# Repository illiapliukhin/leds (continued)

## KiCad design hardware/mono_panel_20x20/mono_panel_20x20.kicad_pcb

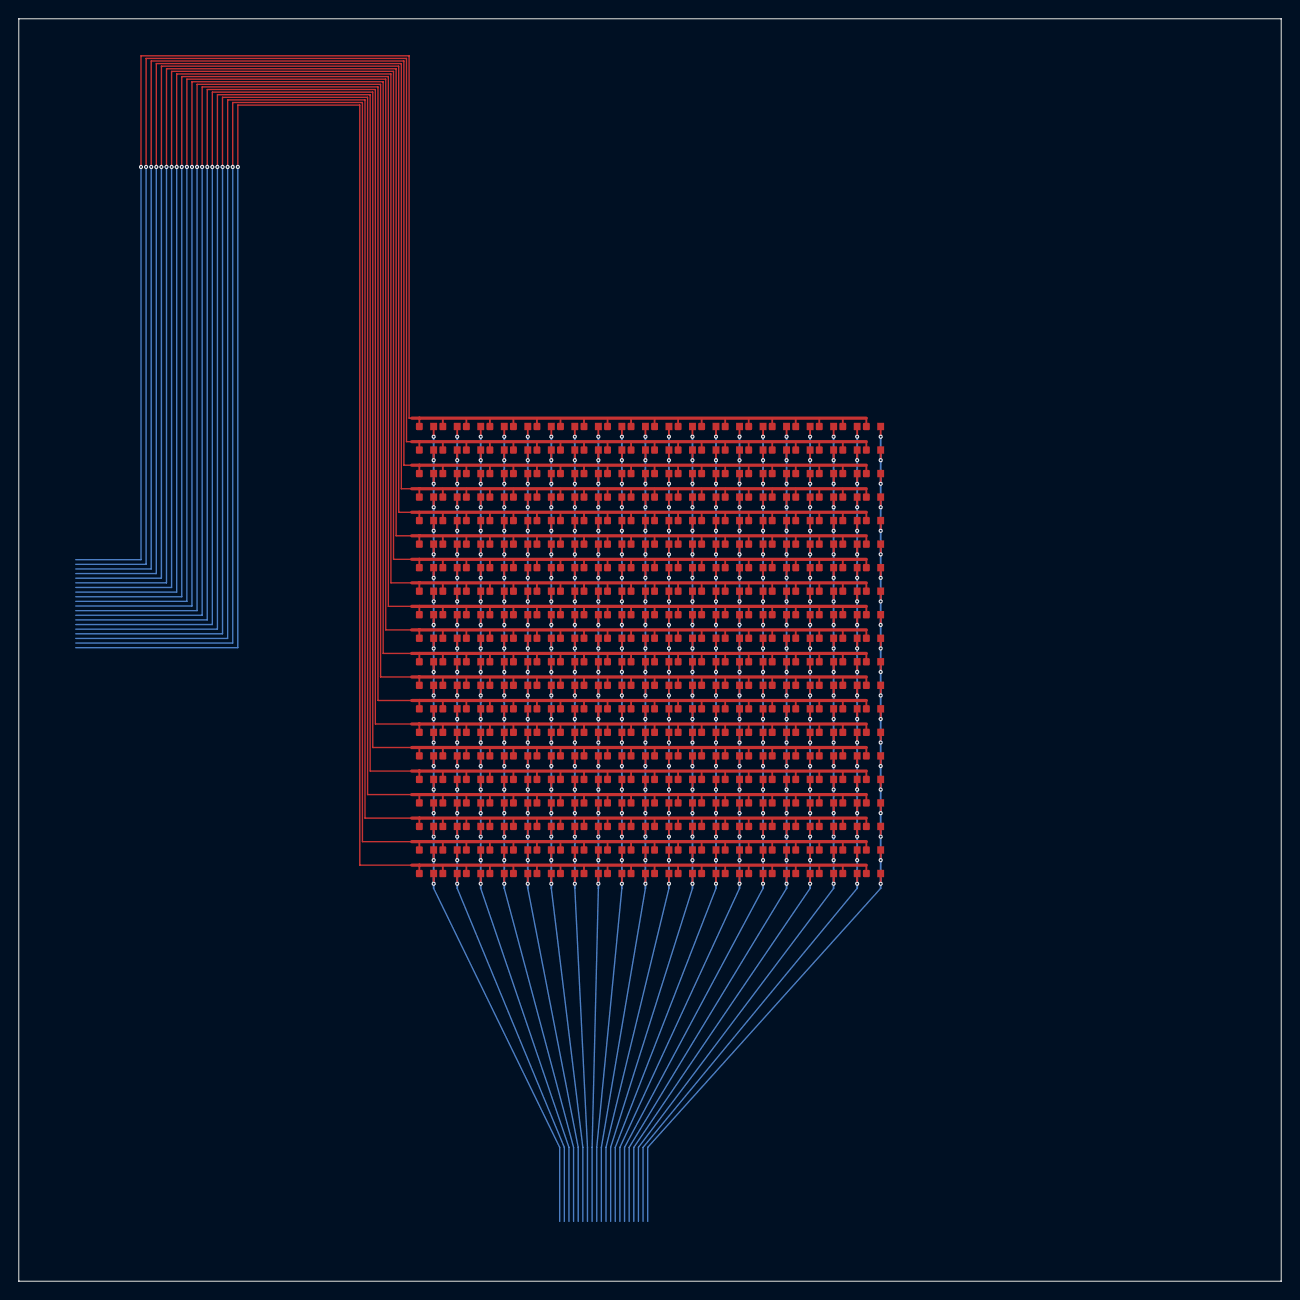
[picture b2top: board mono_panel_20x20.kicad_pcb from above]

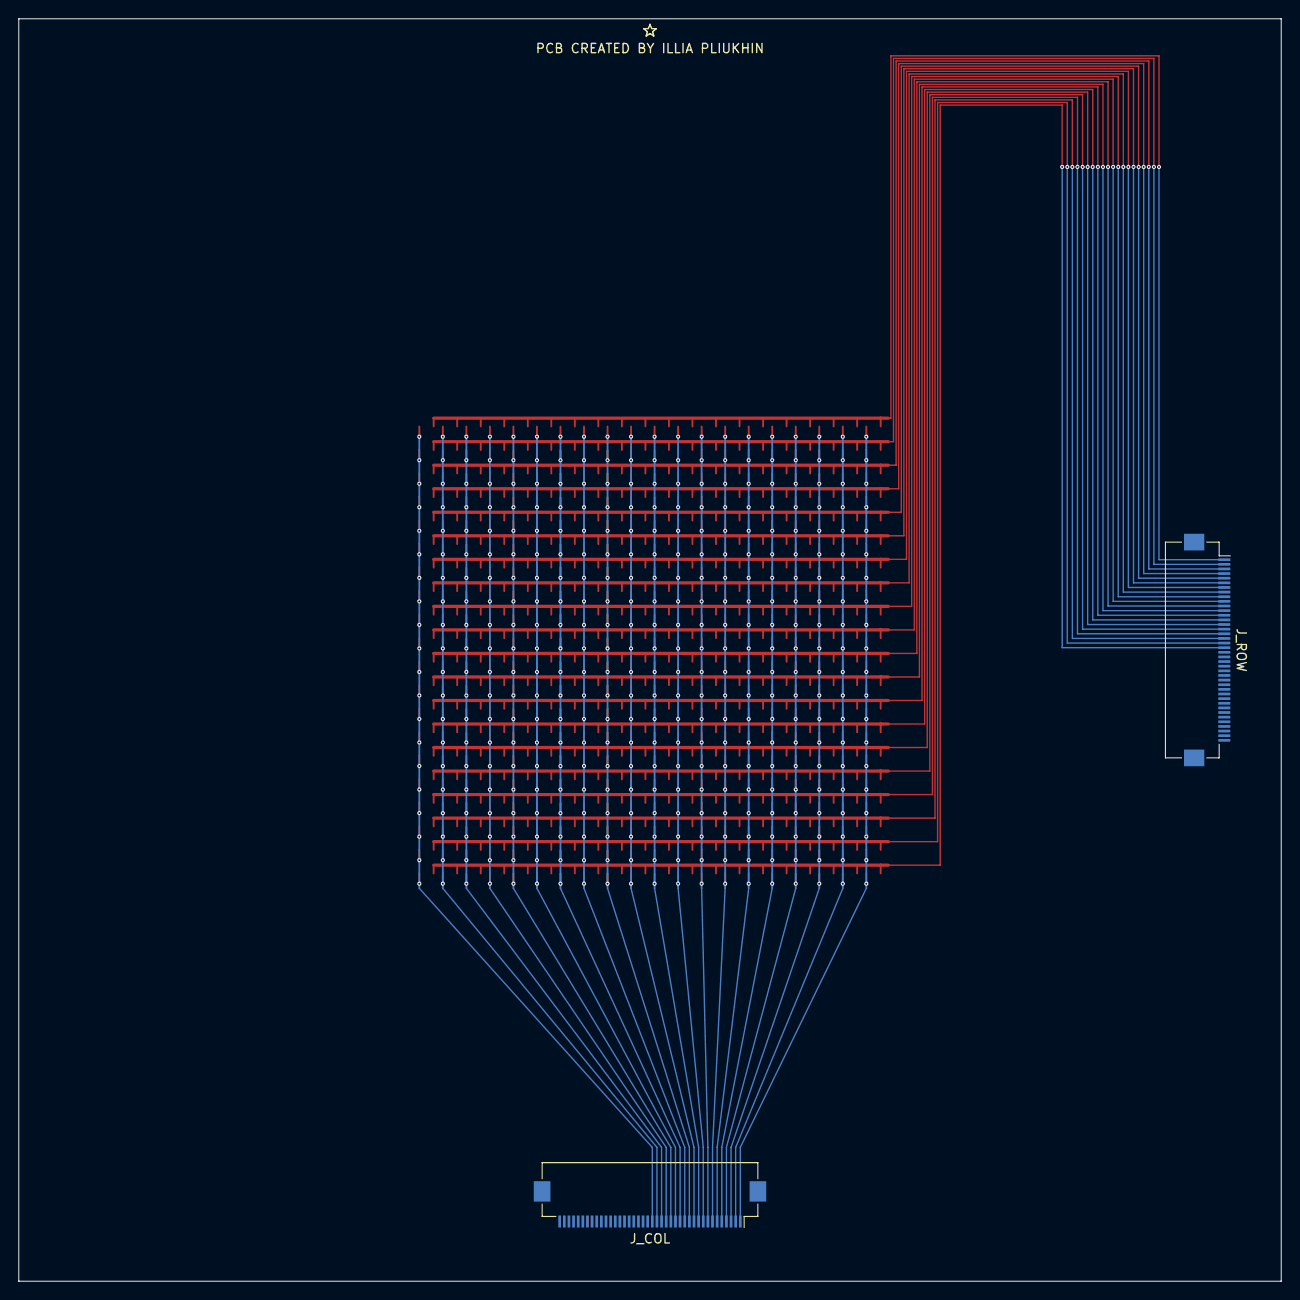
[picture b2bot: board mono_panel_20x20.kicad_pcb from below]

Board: 2 copper layers, 136.3 x 136.3 mm, 402 parts (2 on the bottom side), 40 nets.

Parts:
D1, D2, D3, D4, D5, D6, D7, D8, D9, D10, D11, D12, D13, D14, D15, D16, D17, D18, D19, D20, D21, D22, D23, D24, D25, D26, D27, D28, D29, D30, D31, D32, D33, D34, D35, D36, D37, D38, D39, D40, D41, D42, D43, D44, D45, D46, D47, D48, D49, D50, D51, D52, D53, D54, D55, D56, D57, D58, D59, D60, D61, D62, D63, D64, D65, D66, D67, D68, D69, D70, D71, D72, D73, D74, D75, D76, D77, D78, D79, D80, D81, D82, D83, D84, D85, D86, D87, D88, D89, D90, D91, D92, D93, D94, D95, D96, D97, D98, D99, D100, D101, D102, D103, D104, D105, D106, D107, D108, D109, D110, D111, D112, D113, D114, D115, D116, D117, D118, D119, D120, D121, D122, D123, D124, D125, D126, D127, D128, D129, D130, D131, D132, D133, D134, D135, D136, D137, D138, D139, D140, D141, D142, D143, D144, D145, D146, D147, D148, D149, D150, D151, D152, D153, D154, D155, D156, D157, D158, D159, D160, D161, D162, D163, D164, D165, D166, D167, D168, D169, D170, D171, D172, D173, D174, D175, D176, D177, D178, D179, D180, D181, D182, D183, D184, D185, D186, D187, D188, D189, D190, D191, D192, D193, D194, D195, D196, D197, D198, D199, D200, D201, D202, D203, D204, D205, D206, D207, D208, D209, D210, D211, D212, D213, D214, D215, D216, D217, D218, D219, D220, D221, D222, D223, D224, D225, D226, D227, D228, D229, D230, D231, D232, D233, D234, D235, D236, D237, D238, D239, D240, D241, D242, D243, D244, D245, D246, D247, D248, D249, D250, D251, D252, D253, D254, D255, D256, D257, D258, D259, D260, D261, D262, D263, D264, D265, D266, D267, D268, D269, D270, D271, D272, D273, D274, D275, D276, D277, D278, D279, D280, D281, D282, D283, D284, D285, D286, D287, D288, D289, D290, D291, D292, D293, D294, D295, D296, D297, D298, D299, D300, D301, D302, D303, D304, D305, D306, D307, D308, D309, D310, D311, D312, D313, D314, D315, D316, D317, D318, D319, D320, D321, D322, D323, D324, D325, D326, D327, D328, D329, D330, D331, D332, D333, D334, D335, D336, D337, D338, D339, D340, D341, D342, D343, D344, D345, D346, D347, D348, D349, D350, D351, D352, D353, D354, D355, D356, D357, D358, D359, D360, D361, D362, D363, D364, D365, D366, D367, D368, D369, D370, D371, D372, D373, D374, D375, D376, D377, D378, D379, D380, D381, D382, D383, D384, D385, D386, D387, D388, D389, D390, D391, D392, D393, D394, D395, D396, D397, D398, D399, D400: NCD0603W1
J_COL: FFC_40P_050_COL
J_ROW: FFC_40P_050_ROW

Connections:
COL_01: D1.1 (K), D21.1 (K), D41.1 (K), D61.1 (K), D81.1 (K), D101.1 (K), D121.1 (K), D141.1 (K), D161.1 (K), D181.1 (K), D201.1 (K), D221.1 (K), D241.1 (K), D261.1 (K), D281.1 (K), D301.1 (K), D321.1 (K), D341.1 (K), D361.1 (K), D381.1 (K), J_COL.1
COL_02: D2.1 (K), D22.1 (K), D42.1 (K), D62.1 (K), D82.1 (K), D102.1 (K), D122.1 (K), D142.1 (K), D162.1 (K), D182.1 (K), D202.1 (K), D222.1 (K), D242.1 (K), D262.1 (K), D282.1 (K), D302.1 (K), D322.1 (K), D342.1 (K), D362.1 (K), D382.1 (K), J_COL.2
COL_03: D3.1 (K), D23.1 (K), D43.1 (K), D63.1 (K), D83.1 (K), D103.1 (K), D123.1 (K), D143.1 (K), D163.1 (K), D183.1 (K), D203.1 (K), D223.1 (K), D243.1 (K), D263.1 (K), D283.1 (K), D303.1 (K), D323.1 (K), D343.1 (K), D363.1 (K), D383.1 (K), J_COL.3
COL_04: D4.1 (K), D24.1 (K), D44.1 (K), D64.1 (K), D84.1 (K), D104.1 (K), D124.1 (K), D144.1 (K), D164.1 (K), D184.1 (K), D204.1 (K), D224.1 (K), D244.1 (K), D264.1 (K), D284.1 (K), D304.1 (K), D324.1 (K), D344.1 (K), D364.1 (K), D384.1 (K), J_COL.4
COL_05: D5.1 (K), D25.1 (K), D45.1 (K), D65.1 (K), D85.1 (K), D105.1 (K), D125.1 (K), D145.1 (K), D165.1 (K), D185.1 (K), D205.1 (K), D225.1 (K), D245.1 (K), D265.1 (K), D285.1 (K), D305.1 (K), D325.1 (K), D345.1 (K), D365.1 (K), D385.1 (K), J_COL.5
COL_06: D6.1 (K), D26.1 (K), D46.1 (K), D66.1 (K), D86.1 (K), D106.1 (K), D126.1 (K), D146.1 (K), D166.1 (K), D186.1 (K), D206.1 (K), D226.1 (K), D246.1 (K), D266.1 (K), D286.1 (K), D306.1 (K), D326.1 (K), D346.1 (K), D366.1 (K), D386.1 (K), J_COL.6
COL_07: D7.1 (K), D27.1 (K), D47.1 (K), D67.1 (K), D87.1 (K), D107.1 (K), D127.1 (K), D147.1 (K), D167.1 (K), D187.1 (K), D207.1 (K), D227.1 (K), D247.1 (K), D267.1 (K), D287.1 (K), D307.1 (K), D327.1 (K), D347.1 (K), D367.1 (K), D387.1 (K), J_COL.7
COL_08: D8.1 (K), D28.1 (K), D48.1 (K), D68.1 (K), D88.1 (K), D108.1 (K), D128.1 (K), D148.1 (K), D168.1 (K), D188.1 (K), D208.1 (K), D228.1 (K), D248.1 (K), D268.1 (K), D288.1 (K), D308.1 (K), D328.1 (K), D348.1 (K), D368.1 (K), D388.1 (K), J_COL.8
COL_09: D9.1 (K), D29.1 (K), D49.1 (K), D69.1 (K), D89.1 (K), D109.1 (K), D129.1 (K), D149.1 (K), D169.1 (K), D189.1 (K), D209.1 (K), D229.1 (K), D249.1 (K), D269.1 (K), D289.1 (K), D309.1 (K), D329.1 (K), D349.1 (K), D369.1 (K), D389.1 (K), J_COL.9
COL_10: D10.1 (K), D30.1 (K), D50.1 (K), D70.1 (K), D90.1 (K), D110.1 (K), D130.1 (K), D150.1 (K), D170.1 (K), D190.1 (K), D210.1 (K), D230.1 (K), D250.1 (K), D270.1 (K), D290.1 (K), D310.1 (K), D330.1 (K), D350.1 (K), D370.1 (K), D390.1 (K), J_COL.10
COL_11: D11.1 (K), D31.1 (K), D51.1 (K), D71.1 (K), D91.1 (K), D111.1 (K), D131.1 (K), D151.1 (K), D171.1 (K), D191.1 (K), D211.1 (K), D231.1 (K), D251.1 (K), D271.1 (K), D291.1 (K), D311.1 (K), D331.1 (K), D351.1 (K), D371.1 (K), D391.1 (K), J_COL.11
COL_12: D12.1 (K), D32.1 (K), D52.1 (K), D72.1 (K), D92.1 (K), D112.1 (K), D132.1 (K), D152.1 (K), D172.1 (K), D192.1 (K), D212.1 (K), D232.1 (K), D252.1 (K), D272.1 (K), D292.1 (K), D312.1 (K), D332.1 (K), D352.1 (K), D372.1 (K), D392.1 (K), J_COL.12
COL_13: D13.1 (K), D33.1 (K), D53.1 (K), D73.1 (K), D93.1 (K), D113.1 (K), D133.1 (K), D153.1 (K), D173.1 (K), D193.1 (K), D213.1 (K), D233.1 (K), D253.1 (K), D273.1 (K), D293.1 (K), D313.1 (K), D333.1 (K), D353.1 (K), D373.1 (K), D393.1 (K), J_COL.13
COL_14: D14.1 (K), D34.1 (K), D54.1 (K), D74.1 (K), D94.1 (K), D114.1 (K), D134.1 (K), D154.1 (K), D174.1 (K), D194.1 (K), D214.1 (K), D234.1 (K), D254.1 (K), D274.1 (K), D294.1 (K), D314.1 (K), D334.1 (K), D354.1 (K), D374.1 (K), D394.1 (K), J_COL.14
COL_15: D15.1 (K), D35.1 (K), D55.1 (K), D75.1 (K), D95.1 (K), D115.1 (K), D135.1 (K), D155.1 (K), D175.1 (K), D195.1 (K), D215.1 (K), D235.1 (K), D255.1 (K), D275.1 (K), D295.1 (K), D315.1 (K), D335.1 (K), D355.1 (K), D375.1 (K), D395.1 (K), J_COL.15
COL_16: D16.1 (K), D36.1 (K), D56.1 (K), D76.1 (K), D96.1 (K), D116.1 (K), D136.1 (K), D156.1 (K), D176.1 (K), D196.1 (K), D216.1 (K), D236.1 (K), D256.1 (K), D276.1 (K), D296.1 (K), D316.1 (K), D336.1 (K), D356.1 (K), D376.1 (K), D396.1 (K), J_COL.16
COL_17: D17.1 (K), D37.1 (K), D57.1 (K), D77.1 (K), D97.1 (K), D117.1 (K), D137.1 (K), D157.1 (K), D177.1 (K), D197.1 (K), D217.1 (K), D237.1 (K), D257.1 (K), D277.1 (K), D297.1 (K), D317.1 (K), D337.1 (K), D357.1 (K), D377.1 (K), D397.1 (K), J_COL.17
COL_18: D18.1 (K), D38.1 (K), D58.1 (K), D78.1 (K), D98.1 (K), D118.1 (K), D138.1 (K), D158.1 (K), D178.1 (K), D198.1 (K), D218.1 (K), D238.1 (K), D258.1 (K), D278.1 (K), D298.1 (K), D318.1 (K), D338.1 (K), D358.1 (K), D378.1 (K), D398.1 (K), J_COL.18
COL_19: D19.1 (K), D39.1 (K), D59.1 (K), D79.1 (K), D99.1 (K), D119.1 (K), D139.1 (K), D159.1 (K), D179.1 (K), D199.1 (K), D219.1 (K), D239.1 (K), D259.1 (K), D279.1 (K), D299.1 (K), D319.1 (K), D339.1 (K), D359.1 (K), D379.1 (K), D399.1 (K), J_COL.19
COL_20: D20.1 (K), D40.1 (K), D60.1 (K), D80.1 (K), D100.1 (K), D120.1 (K), D140.1 (K), D160.1 (K), D180.1 (K), D200.1 (K), D220.1 (K), D240.1 (K), D260.1 (K), D280.1 (K), D300.1 (K), D320.1 (K), D340.1 (K), D360.1 (K), D380.1 (K), D400.1 (K), J_COL.20
ROW_01_ANODE: D1.2 (A), D2.2 (A), D3.2 (A), D4.2 (A), D5.2 (A), D6.2 (A), D7.2 (A), D8.2 (A), D9.2 (A), D10.2 (A), D11.2 (A), D12.2 (A), D13.2 (A), D14.2 (A), D15.2 (A), D16.2 (A), D17.2 (A), D18.2 (A), D19.2 (A), D20.2 (A), J_ROW.1
ROW_02_ANODE: D21.2 (A), D22.2 (A), D23.2 (A), D24.2 (A), D25.2 (A), D26.2 (A), D27.2 (A), D28.2 (A), D29.2 (A), D30.2 (A), D31.2 (A), D32.2 (A), D33.2 (A), D34.2 (A), D35.2 (A), D36.2 (A), D37.2 (A), D38.2 (A), D39.2 (A), D40.2 (A), J_ROW.2
ROW_03_ANODE: D41.2 (A), D42.2 (A), D43.2 (A), D44.2 (A), D45.2 (A), D46.2 (A), D47.2 (A), D48.2 (A), D49.2 (A), D50.2 (A), D51.2 (A), D52.2 (A), D53.2 (A), D54.2 (A), D55.2 (A), D56.2 (A), D57.2 (A), D58.2 (A), D59.2 (A), D60.2 (A), J_ROW.3
ROW_04_ANODE: D61.2 (A), D62.2 (A), D63.2 (A), D64.2 (A), D65.2 (A), D66.2 (A), D67.2 (A), D68.2 (A), D69.2 (A), D70.2 (A), D71.2 (A), D72.2 (A), D73.2 (A), D74.2 (A), D75.2 (A), D76.2 (A), D77.2 (A), D78.2 (A), D79.2 (A), D80.2 (A), J_ROW.4
ROW_05_ANODE: D81.2 (A), D82.2 (A), D83.2 (A), D84.2 (A), D85.2 (A), D86.2 (A), D87.2 (A), D88.2 (A), D89.2 (A), D90.2 (A), D91.2 (A), D92.2 (A), D93.2 (A), D94.2 (A), D95.2 (A), D96.2 (A), D97.2 (A), D98.2 (A), D99.2 (A), D100.2 (A), J_ROW.5
ROW_06_ANODE: D101.2 (A), D102.2 (A), D103.2 (A), D104.2 (A), D105.2 (A), D106.2 (A), D107.2 (A), D108.2 (A), D109.2 (A), D110.2 (A), D111.2 (A), D112.2 (A), D113.2 (A), D114.2 (A), D115.2 (A), D116.2 (A), D117.2 (A), D118.2 (A), D119.2 (A), D120.2 (A), J_ROW.6
ROW_07_ANODE: D121.2 (A), D122.2 (A), D123.2 (A), D124.2 (A), D125.2 (A), D126.2 (A), D127.2 (A), D128.2 (A), D129.2 (A), D130.2 (A), D131.2 (A), D132.2 (A), D133.2 (A), D134.2 (A), D135.2 (A), D136.2 (A), D137.2 (A), D138.2 (A), D139.2 (A), D140.2 (A), J_ROW.7
ROW_08_ANODE: D141.2 (A), D142.2 (A), D143.2 (A), D144.2 (A), D145.2 (A), D146.2 (A), D147.2 (A), D148.2 (A), D149.2 (A), D150.2 (A), D151.2 (A), D152.2 (A), D153.2 (A), D154.2 (A), D155.2 (A), D156.2 (A), D157.2 (A), D158.2 (A), D159.2 (A), D160.2 (A), J_ROW.8
ROW_09_ANODE: D161.2 (A), D162.2 (A), D163.2 (A), D164.2 (A), D165.2 (A), D166.2 (A), D167.2 (A), D168.2 (A), D169.2 (A), D170.2 (A), D171.2 (A), D172.2 (A), D173.2 (A), D174.2 (A), D175.2 (A), D176.2 (A), D177.2 (A), D178.2 (A), D179.2 (A), D180.2 (A), J_ROW.9
ROW_10_ANODE: D181.2 (A), D182.2 (A), D183.2 (A), D184.2 (A), D185.2 (A), D186.2 (A), D187.2 (A), D188.2 (A), D189.2 (A), D190.2 (A), D191.2 (A), D192.2 (A), D193.2 (A), D194.2 (A), D195.2 (A), D196.2 (A), D197.2 (A), D198.2 (A), D199.2 (A), D200.2 (A), J_ROW.10
ROW_11_ANODE: D201.2 (A), D202.2 (A), D203.2 (A), D204.2 (A), D205.2 (A), D206.2 (A), D207.2 (A), D208.2 (A), D209.2 (A), D210.2 (A), D211.2 (A), D212.2 (A), D213.2 (A), D214.2 (A), D215.2 (A), D216.2 (A), D217.2 (A), D218.2 (A), D219.2 (A), D220.2 (A), J_ROW.11
ROW_12_ANODE: D221.2 (A), D222.2 (A), D223.2 (A), D224.2 (A), D225.2 (A), D226.2 (A), D227.2 (A), D228.2 (A), D229.2 (A), D230.2 (A), D231.2 (A), D232.2 (A), D233.2 (A), D234.2 (A), D235.2 (A), D236.2 (A), D237.2 (A), D238.2 (A), D239.2 (A), D240.2 (A), J_ROW.12
ROW_13_ANODE: D241.2 (A), D242.2 (A), D243.2 (A), D244.2 (A), D245.2 (A), D246.2 (A), D247.2 (A), D248.2 (A), D249.2 (A), D250.2 (A), D251.2 (A), D252.2 (A), D253.2 (A), D254.2 (A), D255.2 (A), D256.2 (A), D257.2 (A), D258.2 (A), D259.2 (A), D260.2 (A), J_ROW.13
ROW_14_ANODE: D261.2 (A), D262.2 (A), D263.2 (A), D264.2 (A), D265.2 (A), D266.2 (A), D267.2 (A), D268.2 (A), D269.2 (A), D270.2 (A), D271.2 (A), D272.2 (A), D273.2 (A), D274.2 (A), D275.2 (A), D276.2 (A), D277.2 (A), D278.2 (A), D279.2 (A), D280.2 (A), J_ROW.14
ROW_15_ANODE: D281.2 (A), D282.2 (A), D283.2 (A), D284.2 (A), D285.2 (A), D286.2 (A), D287.2 (A), D288.2 (A), D289.2 (A), D290.2 (A), D291.2 (A), D292.2 (A), D293.2 (A), D294.2 (A), D295.2 (A), D296.2 (A), D297.2 (A), D298.2 (A), D299.2 (A), D300.2 (A), J_ROW.15
ROW_16_ANODE: D301.2 (A), D302.2 (A), D303.2 (A), D304.2 (A), D305.2 (A), D306.2 (A), D307.2 (A), D308.2 (A), D309.2 (A), D310.2 (A), D311.2 (A), D312.2 (A), D313.2 (A), D314.2 (A), D315.2 (A), D316.2 (A), D317.2 (A), D318.2 (A), D319.2 (A), D320.2 (A), J_ROW.16
ROW_17_ANODE: D321.2 (A), D322.2 (A), D323.2 (A), D324.2 (A), D325.2 (A), D326.2 (A), D327.2 (A), D328.2 (A), D329.2 (A), D330.2 (A), D331.2 (A), D332.2 (A), D333.2 (A), D334.2 (A), D335.2 (A), D336.2 (A), D337.2 (A), D338.2 (A), D339.2 (A), D340.2 (A), J_ROW.17
ROW_18_ANODE: D341.2 (A), D342.2 (A), D343.2 (A), D344.2 (A), D345.2 (A), D346.2 (A), D347.2 (A), D348.2 (A), D349.2 (A), D350.2 (A), D351.2 (A), D352.2 (A), D353.2 (A), D354.2 (A), D355.2 (A), D356.2 (A), D357.2 (A), D358.2 (A), D359.2 (A), D360.2 (A), J_ROW.18
ROW_19_ANODE: D361.2 (A), D362.2 (A), D363.2 (A), D364.2 (A), D365.2 (A), D366.2 (A), D367.2 (A), D368.2 (A), D369.2 (A), D370.2 (A), D371.2 (A), D372.2 (A), D373.2 (A), D374.2 (A), D375.2 (A), D376.2 (A), D377.2 (A), D378.2 (A), D379.2 (A), D380.2 (A), J_ROW.19
ROW_20_ANODE: D381.2 (A), D382.2 (A), D383.2 (A), D384.2 (A), D385.2 (A), D386.2 (A), D387.2 (A), D388.2 (A), D389.2 (A), D390.2 (A), D391.2 (A), D392.2 (A), D393.2 (A), D394.2 (A), D395.2 (A), D396.2 (A), D397.2 (A), D398.2 (A), D399.2 (A), D400.2 (A), J_ROW.20
